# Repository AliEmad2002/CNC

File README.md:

# 1. Introduction 
This SW runs CNC milling and drilling machine by G-Code interfacing*.
(not all G-code methods are implemented, only the needed ones)

# 2. Target
Mainly targeted for STM32F103 MCU.

# 3. Main features:
 * Uses SD-Card for file loading. Hence does not need to be connected to a computer.
 * Auto leveling:
   - Not the whole file boundaries are scanned. SW parses the file first and scans only areas that would be engraved.
   - After scanning, level map is saved on SD-Card and could be easily restored.
 * Zero saving:
   - After manually adjusting the zero point, distance between this point and the limit switches is stored on the SD-Card. Hence, if a power loss happens, the zero point could be exaxtly returned to without errors.
 * Spindle soft starting:
   - To avoid startup electrical noises.

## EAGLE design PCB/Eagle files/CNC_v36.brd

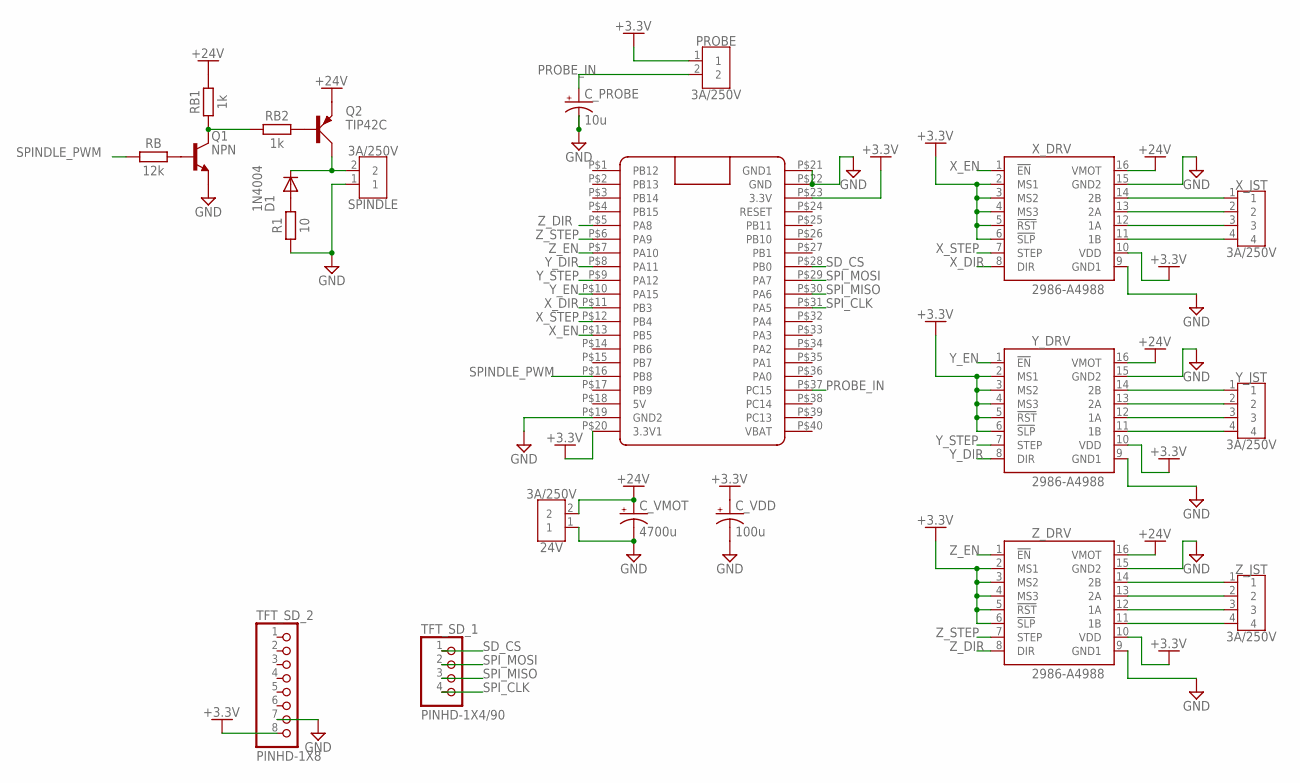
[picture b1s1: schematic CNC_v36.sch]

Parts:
24V: 3A/250V; B2B-XH-A
C_PROBE: 10u; CAPPRD508W65D1000H1100B
C_VDD: 100u; CAPPRD508W65D1000H1100B
C_VMOT: 4700u; CAPPRD550W60D1200H2000B
D1: 1N4004; DO41-10
PROBE: 3A/250V; B2B-XH-A
Q1: NPN; TO92
Q2: TIP42C; TO220AV
R1: 10; RESAD724W46L381D178B
RB: 12k; RESAD724W46L381D178B
RB1, RB2: 1k; RESAD724W46L381D178B
SPINDLE: 3A/250V; B2B-XH-A
TFT_SD_1: PINHD-1X4/90; 1X04/90
TFT_SD_2: PINHD-1X8; 1X08
U$1: BLUE_PILLADVANCED; BLUE_PILL_ADV
X_DRV: 2986-A4988; A4988
X_JST: 3A/250V; B4B-XH-A
Y_DRV: 2986-A4988; A4988
Y_JST: 3A/250V; B4B-XH-A
Z_DRV: 2986-A4988; A4988
Z_JST: 3A/250V; B4B-XH-A

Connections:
+3.3V: C_VDD.1 (+), PROBE.1, TFT_SD_2.8, U$1.P$20 (3.3V1), U$1.P$23 (3.3V), X_DRV.2 (MS1), X_DRV.3 (MS2), X_DRV.4 (MS3), X_DRV.5 (!RST), X_DRV.6 (!SLP), X_DRV.10 (VDD), Y_DRV.2 (MS1), Y_DRV.3 (MS2), Y_DRV.4 (MS3), Y_DRV.5 (!RST), Y_DRV.6 (!SLP), Y_DRV.10 (VDD), Z_DRV.2 (MS1), Z_DRV.3 (MS2), Z_DRV.4 (MS3), Z_DRV.5 (!RST), Z_DRV.6 (!SLP), Z_DRV.10 (VDD)
+24V: 24V.2, C_VMOT.1 (+), Q2.E, RB1.2, X_DRV.16 (VMOT), Y_DRV.16 (VMOT), Z_DRV.16 (VMOT)
GND: 24V.1, C_PROBE.2 (-), C_VDD.2 (-), C_VMOT.2 (-), Q1.1 (E), R1.1, SPINDLE.1, TFT_SD_2.7, U$1.P$19 (GND2), U$1.P$21 (GND1), U$1.P$22 (GND), X_DRV.9 (GND1), X_DRV.15 (GND2), Y_DRV.9 (GND1), Y_DRV.15 (GND2), Z_DRV.9 (GND1), Z_DRV.15 (GND2)
unnamed: Q1.2 (B), RB.2
unnamed: Q1.3 (C), RB1.1, RB2.1
unnamed: D1.A, R1.2
unnamed: D1.C, Q2.C, SPINDLE.2
unnamed: Q2.B, RB2.2
unnamed: Y_DRV.11 (1B), Y_JST.4
unnamed: Y_DRV.12 (1A), Y_JST.3
unnamed: Y_DRV.13 (2A), Y_JST.2
unnamed: Y_DRV.14 (2B), Y_JST.1
unnamed: Z_DRV.11 (1B), Z_JST.4
unnamed: Z_DRV.12 (1A), Z_JST.3
unnamed: Z_DRV.13 (2A), Z_JST.2
unnamed: Z_DRV.14 (2B), Z_JST.1
unnamed: X_DRV.11 (1B), X_JST.4
unnamed: X_DRV.12 (1A), X_JST.3
unnamed: X_DRV.13 (2A), X_JST.2
unnamed: X_DRV.14 (2B), X_JST.1
PROBE_IN: C_PROBE.1 (+), PROBE.2, U$1.P$37 (PC15)
SD_CS: TFT_SD_1.1, U$1.P$28 (PB0)
SPINDLE_PWM: RB.1, U$1.P$16 (PB8)
SPI_CLK: TFT_SD_1.4, U$1.P$31 (PA5)
SPI_MISO: TFT_SD_1.3, U$1.P$30 (PA6)
SPI_MOSI: TFT_SD_1.2, U$1.P$29 (PA7)
X_DIR: U$1.P$11 (PB3), X_DRV.8 (DIR)
X_EN: U$1.P$13 (PB5), X_DRV.1 (!EN)
X_STEP: U$1.P$12 (PB4), X_DRV.7 (STEP)
Y_DIR: U$1.P$8 (PA11), Y_DRV.8 (DIR)
Y_EN: U$1.P$10 (PA15), Y_DRV.1 (!EN)
Y_STEP: U$1.P$9 (PA12), Y_DRV.7 (STEP)
Z_DIR: U$1.P$5 (PA8), Z_DRV.8 (DIR)
Z_EN: U$1.P$7 (PA10), Z_DRV.1 (!EN)
Z_STEP: U$1.P$6 (PA9), Z_DRV.7 (STEP)

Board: 2 copper layers, 22 parts (0 on the bottom side), 35 nets, no tracks yet.

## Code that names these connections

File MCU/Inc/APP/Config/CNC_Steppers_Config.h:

/*
 * CNC_Steppers_Config.h
 *
 *  Created on: Feb 21, 2023
 *      Author: ali20
 */

#ifndef INCLUDE_APP_CONFIG_CNC_STEPPERS_CONFIG_H_
#define INCLUDE_APP_CONFIG_CNC_STEPPERS_CONFIG_H_


/*	stepper motor drivers' pins (slave in our poor pathetic case)	*/

#define X_DIR_PIN							GPIO_Pin_B3
#define X_STEP_PIN							GPIO_Pin_B4
#define X_EN_PIN							GPIO_Pin_B5

#define Y_DIR_PIN							GPIO_Pin_A0
#define Y_STEP_PIN							GPIO_Pin_A1
#define Y_EN_PIN							GPIO_Pin_A8

#define Z_DIR_PIN							GPIO_Pin_A9
#define Z_STEP_PIN							GPIO_Pin_A8
#define Z_EN_PIN							GPIO_Pin_A10

/*	spindles driving PWM signal	*/
#define SPINDLE_PWM_TIM_UNIT_NUMBER			4
#define SPINDLE_PWM_TIM_CHANNEL				TIM_Channel_1
#define SPINDLE_PWM_AFIO_MAP				0

/*	How frequently will speed be changed, in steps	*/
#define SPEED_CHANGE_DELTA		 			64

/*	steps per mm (initial, and could be changed by g-code later)	*/
#define STEPS_PER_MM						800

/*	minimum operating speed	*/
#define SPEED_MIN							(STEPS_PER_MM/4) // 0.25mm/sec




#endif /* INCLUDE_APP_CONFIG_CNC_STEPPERS_CONFIG_H_ */

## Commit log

2023-01-12 added G-code generator files
2023-02-21 Layered things a bit more. Updated Stack
2023-02-21 Added a copy of COTS code
2023-02-21 Layered things a bit more
2023-02-25 Added Notes
2023-02-25 made code more readable
2023-02-26 Updated Queue program
2023-02-27 updated Queue
2023-02-27 minor
2023-03-30 Create Acknowledgement
2023-03-30 Rename Acknowledgement to Acknowledgement.md
2023-04-02 added "DC_Motor"
2023-04-02 added "spindle"
2023-04-12 added tool changing with retaining level map
2023-04-13 lab work
2023-04-13 added manual probing
2023-04-17 added "PCB"
2023-04-19 now G0 & G1 can have any number of arguments
2023-04-19 Added G_code file input
2023-04-20 layering enhance v1
2023-04-20 layering enhance v2
2023-04-21 added unit changing by G-code
2023-04-22 added trajectory planning
2023-04-23 made progress in trajectory planning function
2023-04-24 progress in SD-card reading
2023-04-26 added CRC calculation
2023-04-27 progress in "SD-Card"
2023-04-27 progress in SDC
2023-04-27 done SDC_Init
2023-04-28 added SDC read/write
2023-04-29 Progress in SDCStream
2023-04-30 SDC V0.0 Done
2023-04-30 SDC V0.1
2023-05-01 added SDC_Test0
2023-05-01 done SDC V0.2
2023-05-01 added SDC_GetLine
2023-05-03 progress in trajectory planning
2023-05-04 Archived "Windows UI"
2023-05-07 added UART interface
2023-05-08 fixed bug in trajectory planning
2023-05-09 Added tool changing. Fixed a bug in "LevelMap"
2023-05-10 Fixed a bug in SD-Card driver
    Entries in FAT were wrongly accessed. Now fixed.
2023-05-11 fixed bugs in trajectory execution
2023-05-16 Fixed speed estimation angle bug.
2023-06-04 added matlab sim files
2023-06-04 Added simulation handling to MCU code
2023-06-04 Updated auto leveling trimming method
2023-06-07 Fixed a bug in stream reading
2023-06-07 Added test files
2023-06-08 Added archive folder
2023-06-08 Added non-OS MCU code to Archive
2023-06-19 reverted to previous version
    This reverts commit 23adb79e1e72adf4c913c1799d391b5c109218b7.
2023-06-19 Added 2mm Test PCB
2023-06-19 Added one-fast, one-saccurate probing mode
2023-06-20 Added 2mm single track
2023-07-01 Last change before implementing the fast sampling mode
2023-07-01 Revert "Last change before implementing the fast sampling mode"
    This reverts commit 0d552d0396f81918241a5bf06e4efd271e9fd777.
2023-07-01 Revert "Revert "Last change before implementing the fast sampling mode""
    This reverts commit cec02d15130ff62c6711ee41309a9389b8b25169.
2023-07-11 Fixed z-referencing bug
2023-07-14 Fixed z-offset error accumulating bug
2023-07-14 Added templates
2023-07-14 Done UI
2023-07-18 Added limit switches
2023-07-18 CONFIGURED PINS
2023-07-23 added Top PCB
